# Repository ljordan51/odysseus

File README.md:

# odysseus
CNC mill/lathe combo for machining detailed features.

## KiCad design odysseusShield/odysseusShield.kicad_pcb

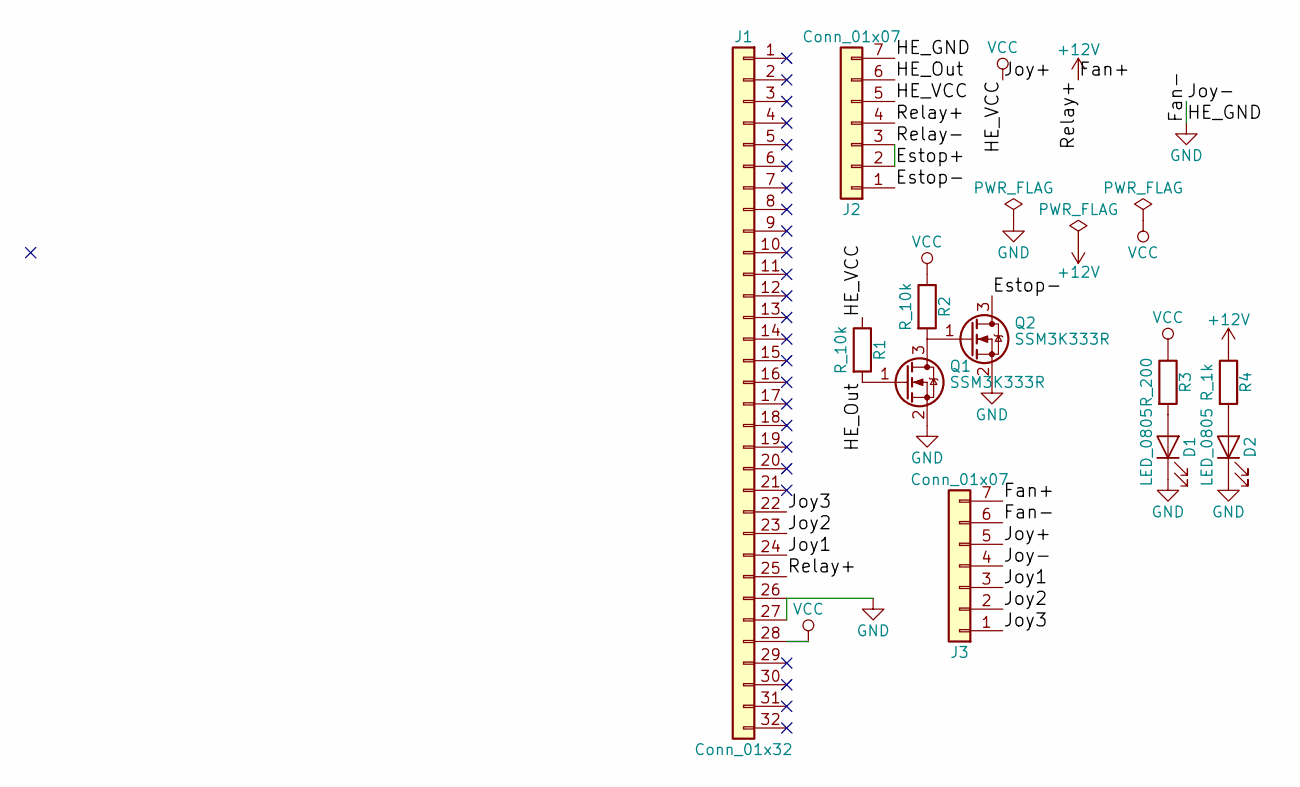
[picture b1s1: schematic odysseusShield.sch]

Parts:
D1, D2: LED_0805; LED_0805_OEM; MPN 475-1410-1-ND
J1: Conn_01x32; Header_Arduino_Shield
J2, J3: Conn_01x07; Header_P2.54mm_7
Q1, Q2: SSM3K333R; SOT-23F; MPN SSM3K333RLFCT-ND
R1, R2: R_10k; R_0805_OEM; MPN CRS0805-FX-1002ELFCT-ND
R3: R_200; R_0805_OEM; MPN RMCF0805JT200RCT-ND
R4: R_1k; R_0805_OEM; MPN RNCP0805FTD1K00CT-ND

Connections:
+12V: J1.25, J2.4, J3.7, R4.1
/Estop+: J2.2, J2.3
/Estop-: J2.1, Q2.3 (D)
/HE_Out: J2.6, Q1.1 (G), R1.2
/Joy1: J1.24, J3.3
/Joy2: J1.23, J3.2
/Joy3: J1.22, J3.1
GND: D1.1 (K), D2.1 (K), J1.26, J1.27, J2.7, J3.4, J3.6, Q1.2 (S), Q2.2 (S)
unnamed: D1.2 (A), R3.2
unnamed: D2.2 (A), R4.2
unnamed: Q1.3 (D), Q2.1 (G), R2.2
VCC: J1.28, J2.5, J3.5, R1.1, R2.1, R3.1

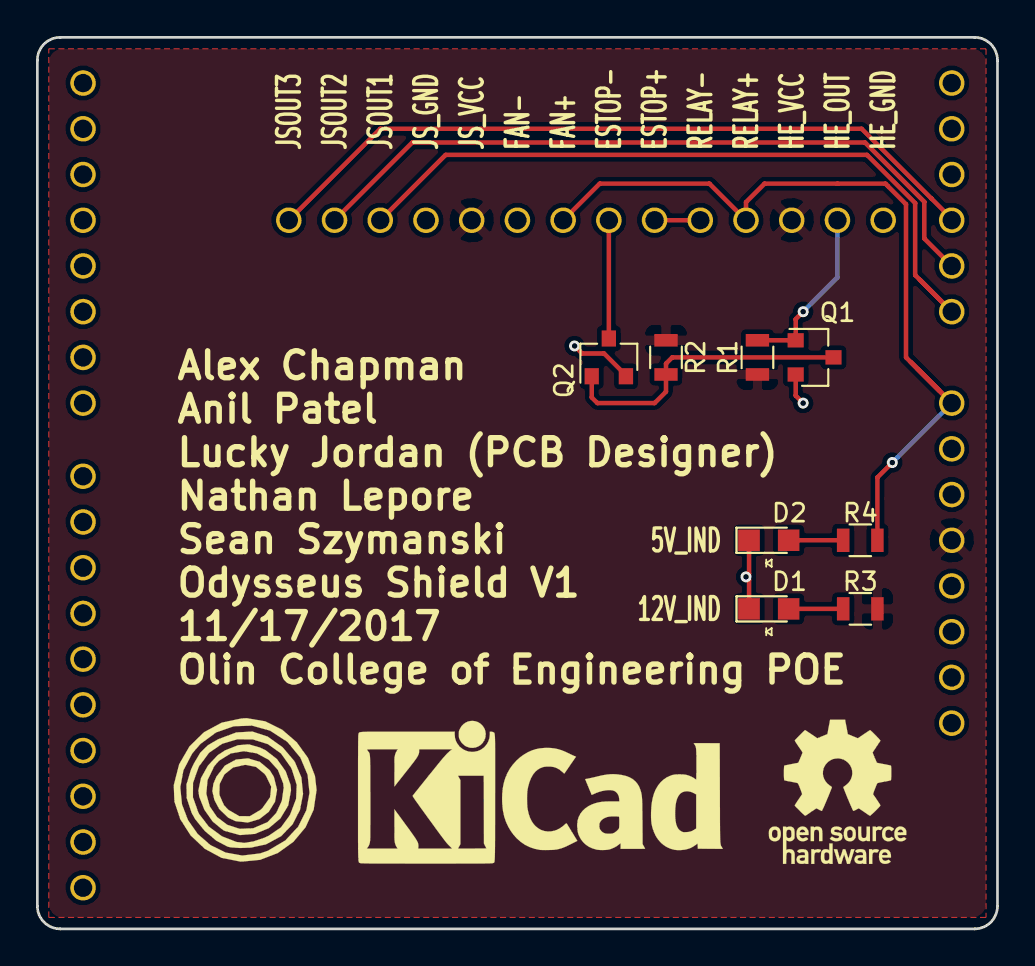
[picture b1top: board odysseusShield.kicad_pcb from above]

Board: 2 copper layers, 53.3 x 49.5 mm, 11 parts (0 on the bottom side), 12 nets.

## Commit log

2017-10-23 added grbl library to drive steppers
2017-10-25 testing with stan's code, added script for continuous motion in two axes at different speeds
2017-10-26 changed myfirststepper to just spin y axis, added machine flat code
2017-10-26 added circular machining script
2017-10-26 added script to run X backward for resetting purposes
2017-10-26 fixed machinecircle
2017-10-27 made minor edits to moveXbackward, fixed machineflat to make multiple passes, tested and edited machine circle (works well)
2017-10-31 working on sprint reviews
2017-11-07 adding code to read hall effect sensor
2017-11-08 added machine cylinder, got rid of zip files
2017-11-09 machine cylinder works, edits to moveXbackward
2017-11-09 added machine cone (untested)
2017-11-09 edits to machine cone, added first flexy stepper, changes speed as function of time
2017-11-12 got flexy stepper working to dynamically change speed/accel/dir also started working on sphere, reduced feed rate and cut depth of cylinder to prevent overtorquing motors
2017-11-12 made pcb and exported gerber files, need to zip and order
2017-11-12 generated zip and tested on oshpark, need to order
2017-11-14 Block Diagram.xml
2017-11-17 Joystick Code
2017-11-19 working on adding logo to PCB, edited PCB based on joystick and fan additions
2017-11-19 finished PCB silkscreen, exported gerbers and confirmed on oshpark, ready to be ordered on pcbway
2017-11-19 added labels to pins and indicator leds
2017-11-20 added some more silk screen stuff
2017-11-28 started sketch for machine sphere, first pass and test of zeroing, having issues
2017-11-28 working with interrupts to figure out zeroing code
2017-11-28 zeroing test 2 with different strategy works
2017-11-29 finalized zeroingtest2 and tested, added comments and cleaned code to reduce lines and run time
2017-12-01 Added Odysseus_Block_Diagram.xml
2017-12-01 Added Odysseus_Block_Diagram.png
2017-12-01 just testing stuff
2017-12-01 testing edits, machine cone tested and works
2017-12-04 some edit to cylinder
2017-12-07 fully integrated electrical system, tested with all scripts and updated pins, fixed zeroing so that there is no more bouncing on switching direction
2017-12-08 edits to moveXbackward for testing purposes
2017-12-10 machine sphere still has bugs, drawing straight line
2017-12-11 working semi-circle
2017-12-11 fixed circle to be based of correct speed
2017-12-11 circle now changes direction based on derivative
2017-12-11 generalized parametric calculates and return max and min vals, although we are changing this approach
2017-12-11 facing works for generalized parametric, need to move on to thinking about handling changes in direction and maximum cut depth, need to consider bit usage, also fixed cylinder for new x direction
